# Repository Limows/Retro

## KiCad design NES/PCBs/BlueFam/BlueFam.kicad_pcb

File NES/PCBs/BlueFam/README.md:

# BlueFam

Project of making AV mod for original Famicom with custom blue body.

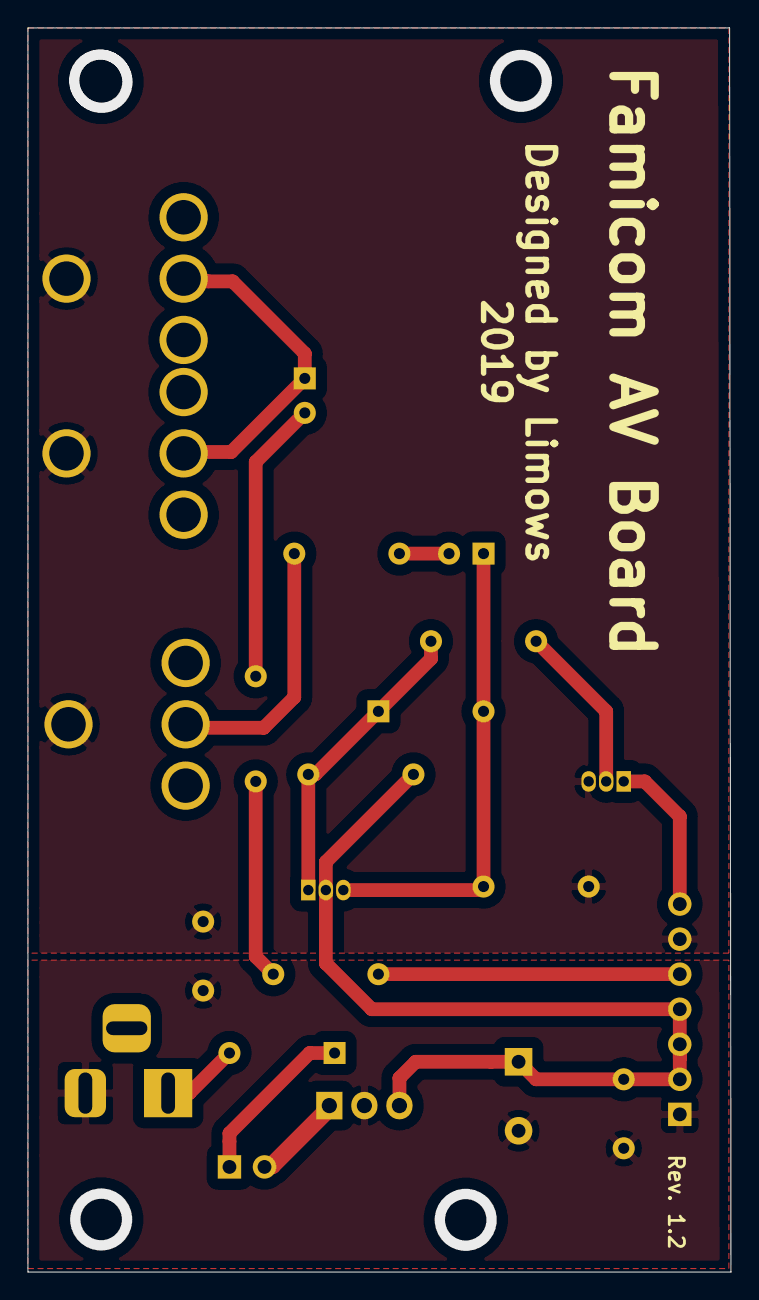
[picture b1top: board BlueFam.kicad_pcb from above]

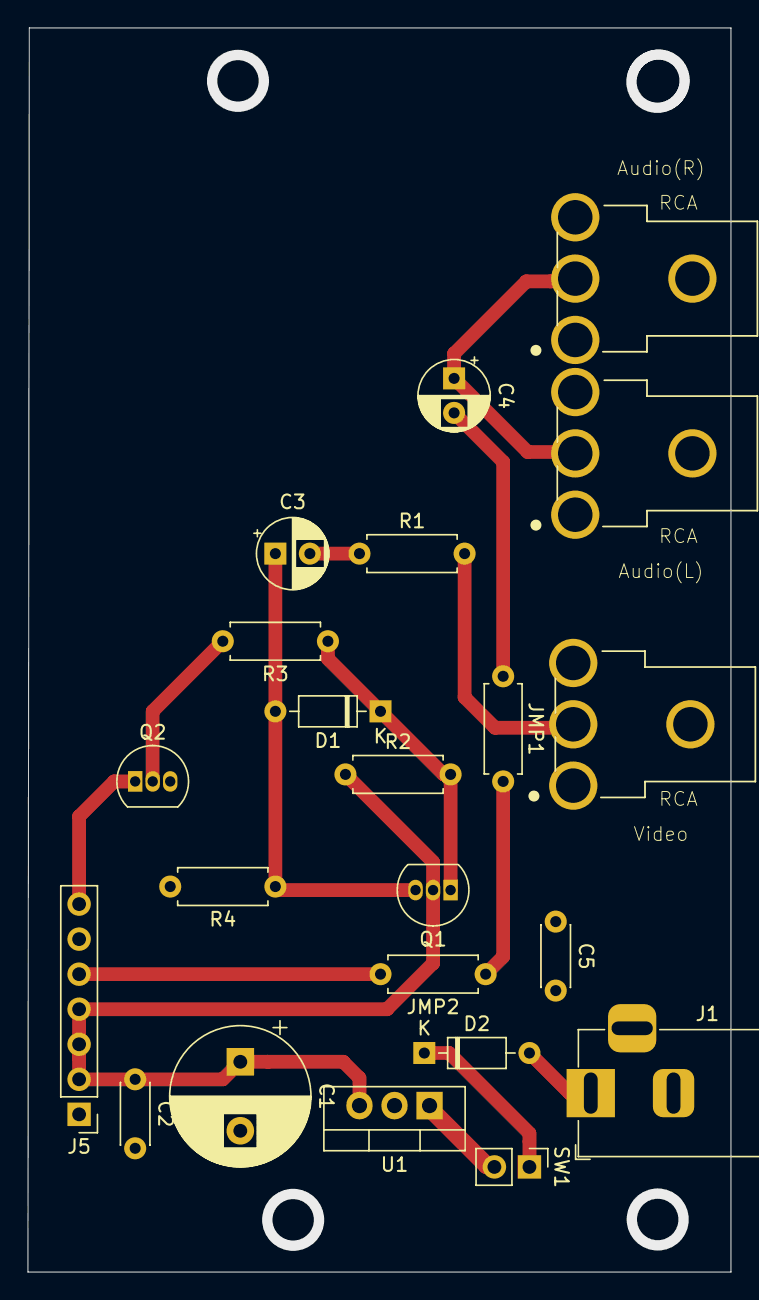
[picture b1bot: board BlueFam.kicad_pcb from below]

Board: 2 copper layers, 51.0 x 90.2 mm, 22 parts (22 on the bottom side), 16 nets.

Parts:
Audio(L): RCA; CUI_RCJ-014
Audio(R): RCA; CUI_RCJ-014
C1: 1000 uF; CP_Radial_D10.0mm_P5.00mm
C2, C5: 100 nF; C_Disc_D4.3mm_W1.9mm_P5.00mm
C3: 220 uF; CP_Radial_D5.0mm_P2.50mm
C4: 47 uF; CP_Radial_D5.0mm_P2.50mm
D1, D2: D; D_DO-35_SOD27_P7.62mm_Horizontal
J1: 9V DC Jack; BarrelJack_Horizontal
J5: To Board; PinHeader_1x07_P2.54mm_Vertical
JMP1, JMP2: 0; R_Axial_DIN0207_L6.3mm_D2.5mm_P7.62mm_Horizontal
Q1: A1266; TO-92_Inline
Q2: C9018; TO-92_Inline
R1: 75; R_Axial_DIN0207_L6.3mm_D2.5mm_P7.62mm_Horizontal
R2: 2K2; R_Axial_DIN0207_L6.3mm_D2.5mm_P7.62mm_Horizontal
R3: 220; R_Axial_DIN0207_L6.3mm_D2.5mm_P7.62mm_Horizontal
R4: 68; R_Axial_DIN0207_L6.3mm_D2.5mm_P7.62mm_Horizontal
SW1: PWR_SW; PinHeader_1x02_P2.54mm_Vertical
U1: L7805; TO-220-3_Vertical
Video: RCA; CUI_RCJ-014

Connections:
GND: C1.2, C2.2, C5.2, J1.2, J5.1, U1.2
GNDA: Audio(L).1C, Audio(R).1C, C5.1, J5.6, Q2.3, R4.2, Video.1C
unnamed: Audio(L).2, Audio(R).2, C4.1
unnamed: C1.1, C2.1, J5.2, J5.3, J5.4, Q1.2, R2.1, U1.3
unnamed: C3.1, D1.2, Q1.3, R4.1
unnamed: C3.2, R1.1
unnamed: C4.2, JMP1.1
unnamed: D1.1, Q1.1, R2.2, R3.1
unnamed: D2.1, SW1.1
unnamed: D2.2, J1.1
unnamed: J5.5, JMP2.2
unnamed: J5.7, Q2.1
unnamed: JMP1.2, JMP2.1
unnamed: Q2.2, R3.2
unnamed: R1.2, Video.2
unnamed: SW1.2, U1.1

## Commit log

2019-11-15 Add Apogee rom cart PCB project
2020-12-23 Added BlueFam project
